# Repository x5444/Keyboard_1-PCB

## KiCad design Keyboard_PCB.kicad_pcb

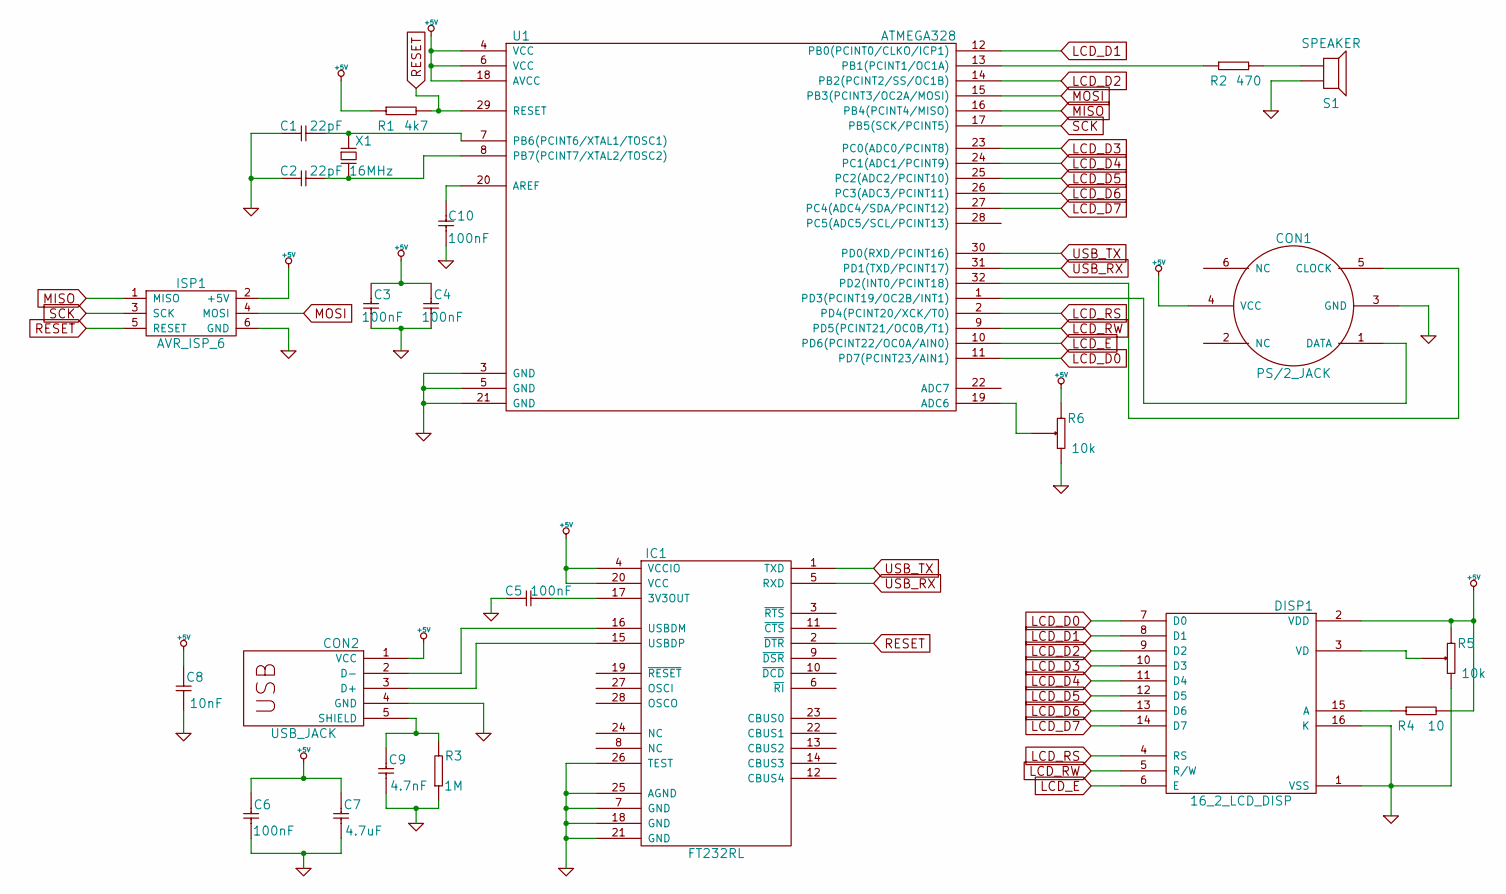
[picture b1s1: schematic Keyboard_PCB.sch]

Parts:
C1, C2, C3, C4, C5, C6, C7, C8, C9, C10: CAPACITOR
CON1: PS/2_JACK
CON2: USB_JACK
DISP1: 16_2_LCD_DISP
IC1: FT232RL
ISP1: AVR_ISP_6
R1, R2, R3, R4: RESISTOR
R5, R6: RESISTOR_VAR
S1: SPEAKER
U1: ATMEGA328
X1: CRYSTAL

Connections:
+5V: C3.1, C4.1, C6.1, C7.1, C8.1, CON1.4 (VCC), CON2.1 (VCC), DISP1.2 (VDD), IC1.4 (VCCIO), IC1.20 (VCC), ISP1.2 (+5V), R1.1, R4.2, R5.3, R6.3, U1.4 (VCC), U1.6 (VCC), U1.18 (AVCC)
GND: C1.1, C2.1, C3.2, C4.2, C5.1, C6.2, C7.2, C8.2, C9.2, C10.2, CON1.3 (GND), CON2.4 (GND), DISP1.1 (VSS), DISP1.16 (K), IC1.7 (GND), IC1.18 (GND), IC1.21 (GND), IC1.25 (AGND), IC1.26 (TEST), ISP1.6 (GND), R3.1, R5.1, R6.1, S1.2, U1.3 (GND), U1.5 (GND), U1.21 (GND)
LCD_D0: DISP1.7 (D0), U1.11 (PD7(PCINT23/AIN1))
LCD_D1: DISP1.8 (D1), U1.12 (PB0(PCINT0/CLKO/ICP1))
LCD_D2: DISP1.9 (D2), U1.14 (PB2(PCINT2/SS/OC1B))
LCD_D3: DISP1.10 (D3), U1.23 (PC0(ADC0/PCINT8))
LCD_D4: DISP1.11 (D4), U1.24 (PC1(ADC1/PCINT9))
LCD_D5: DISP1.12 (D5), U1.25 (PC2(ADC2/PCINT10))
LCD_D6: DISP1.13 (D6), U1.26 (PC3(ADC3/PCINT11))
LCD_D7: DISP1.14 (D7), U1.27 (PC4(ADC4/SDA/PCINT12))
LCD_E: DISP1.6 (E), U1.10 (PD6(PCINT22/OC0A/AIN0))
LCD_RS: DISP1.4 (RS), U1.2 (PD4(PCINT20/XCK/T0))
LCD_RW: DISP1.5 (R/W), U1.9 (PD5(PCINT21/OC0B/T1))
MISO: ISP1.1 (MISO), U1.16 (PB4(PCINT4/MISO))
MOSI: ISP1.4 (MOSI), U1.15 (PB3(PCINT3/OC2A/MOSI))
unnamed: C5.2, IC1.17 (3V3OUT)
unnamed: CON2.2 (D-), IC1.16 (USBDM)
unnamed: CON2.3 (D+), IC1.15 (USBDP)
unnamed: R2.1, U1.13 (PB1(PCINT1/OC1A))
unnamed: CON1.5 (CLOCK), U1.32 (PD2(INT0/PCINT18))
unnamed: R2.2, S1.1
unnamed: CON1.1 (DATA), U1.1 (PD3(PCINT19/OC2B/INT1))
unnamed: DISP1.3 (VD), R5.2
unnamed: R6.2, U1.19 (ADC6)
unnamed: C10.1, U1.20 (AREF)
unnamed: DISP1.15 (A), R4.1
unnamed: C9.1, CON2.5 (SHIELD), R3.2
unnamed: C1.2, U1.7 (PB6(PCINT6/XTAL1/TOSC1)), X1.1
unnamed: C2.2, U1.8 (PB7(PCINT7/XTAL2/TOSC2)), X1.2
RESET: IC1.2 (~DTR), ISP1.5 (RESET), R1.2, U1.29 (RESET)
SCK: ISP1.3 (SCK), U1.17 (PB5(SCK/PCINT5))
USB_RX: IC1.5 (RXD), U1.31 (PD1(TXD/PCINT17))
USB_TX: IC1.1 (TXD), U1.30 (PD0(RXD/PCINT16))

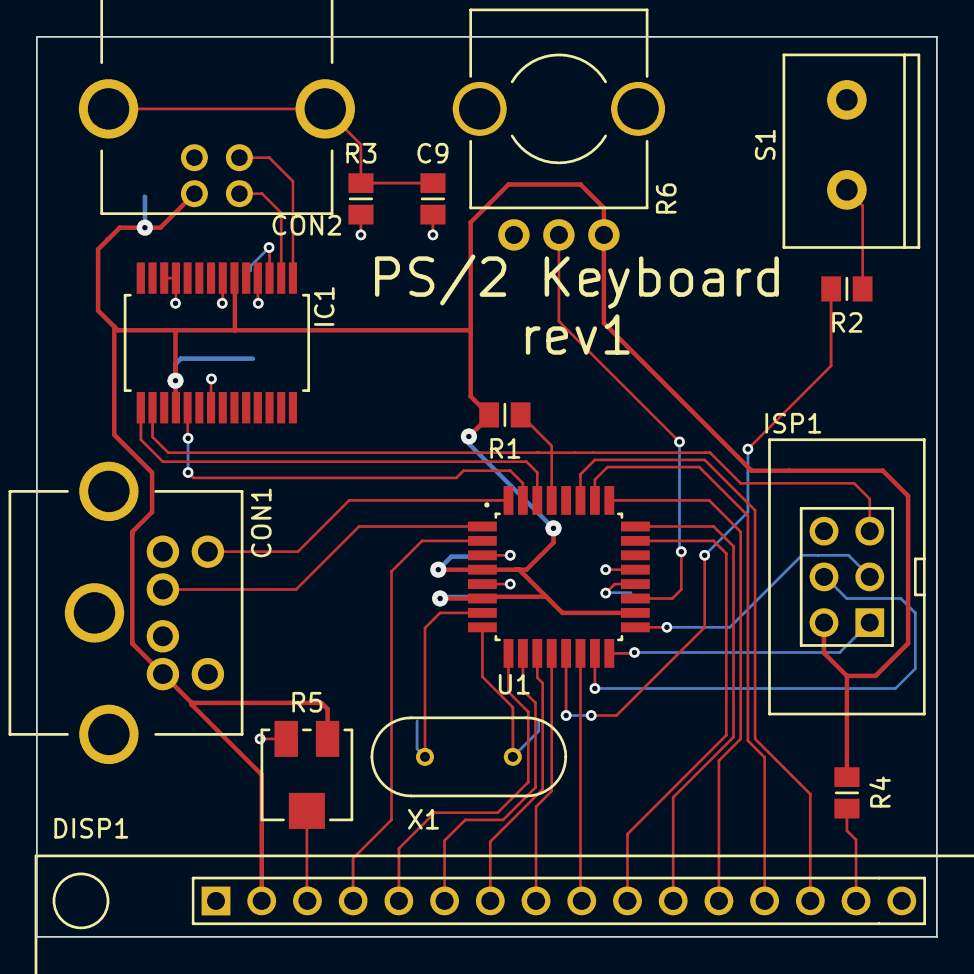
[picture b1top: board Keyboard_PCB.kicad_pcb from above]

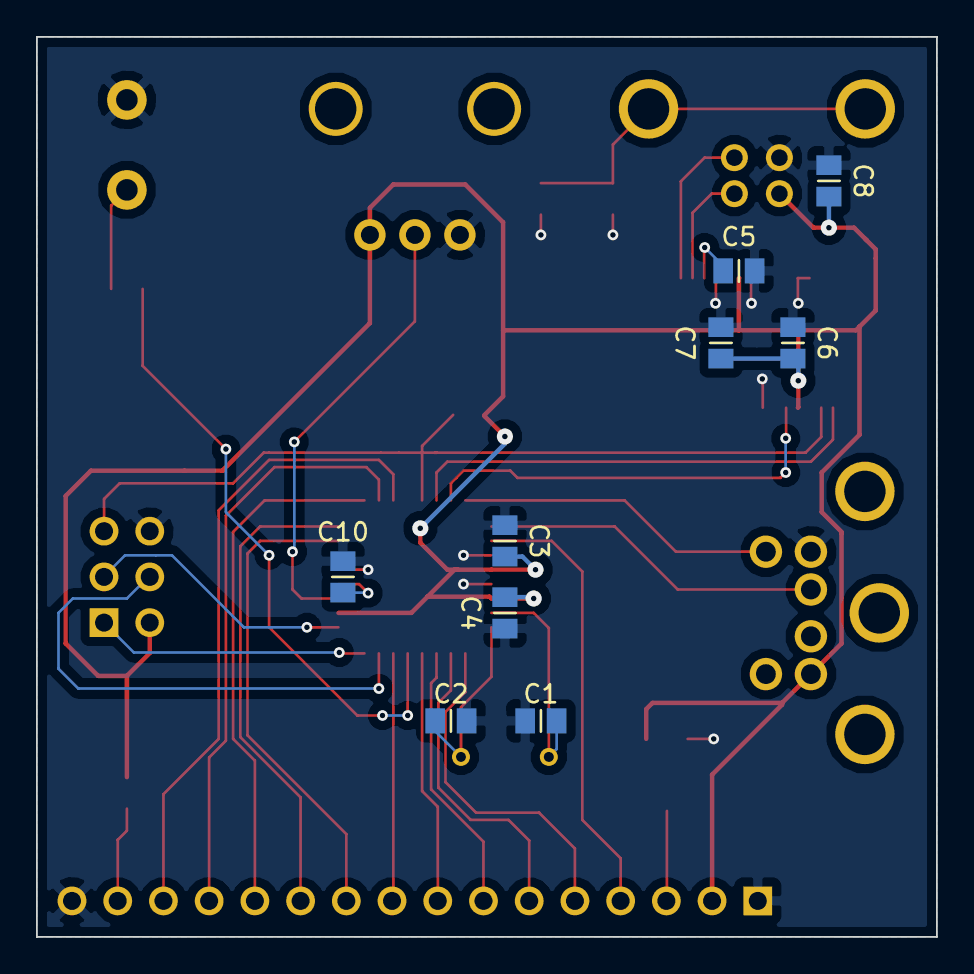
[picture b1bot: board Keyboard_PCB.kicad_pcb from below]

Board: 2 copper layers, 50.0 x 50.0 mm, 24 parts (9 on the bottom side), 33 nets.

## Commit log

2013-10-01 Initial commit.
2013-10-05 Changed things.
2013-10-05 Added FTDI and USB
2013-10-05 Added LCD Circuit.
2013-10-06 changed stuff.
2013-10-06 added .cmp .kicad_pcb .net .
2013-10-07 Didn't change much, just a bit.
2013-10-07 Finished assining Footprints to the schematic symbols.
2013-10-11 Placed and routed signals.
2013-10-11 Added power routes and made it pass DRC.
2013-10-11 Placed text.
2013-10-11 Added description and exported files.
2013-10-11 Exported rev1 release.
2013-10-14 Added BOM.
2013-10-14 Added shopping cart.
